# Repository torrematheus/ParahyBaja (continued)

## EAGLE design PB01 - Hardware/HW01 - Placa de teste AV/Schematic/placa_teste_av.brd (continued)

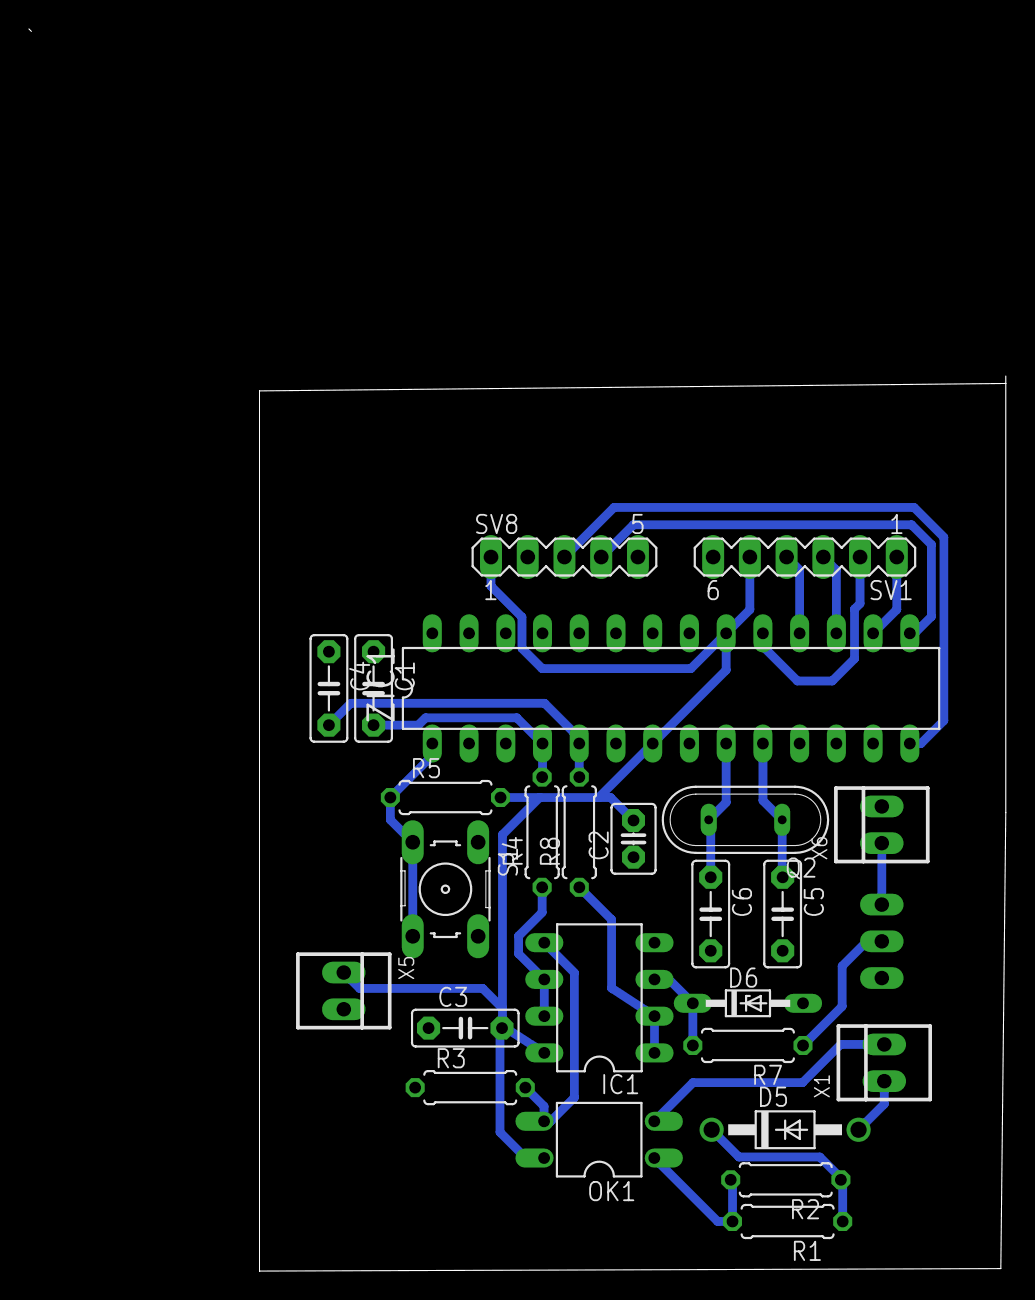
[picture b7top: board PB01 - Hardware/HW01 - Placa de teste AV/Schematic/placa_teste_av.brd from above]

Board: 2 copper layers, 51.6 x 61.4 mm, 26 parts (1 on the bottom side), 23 nets.

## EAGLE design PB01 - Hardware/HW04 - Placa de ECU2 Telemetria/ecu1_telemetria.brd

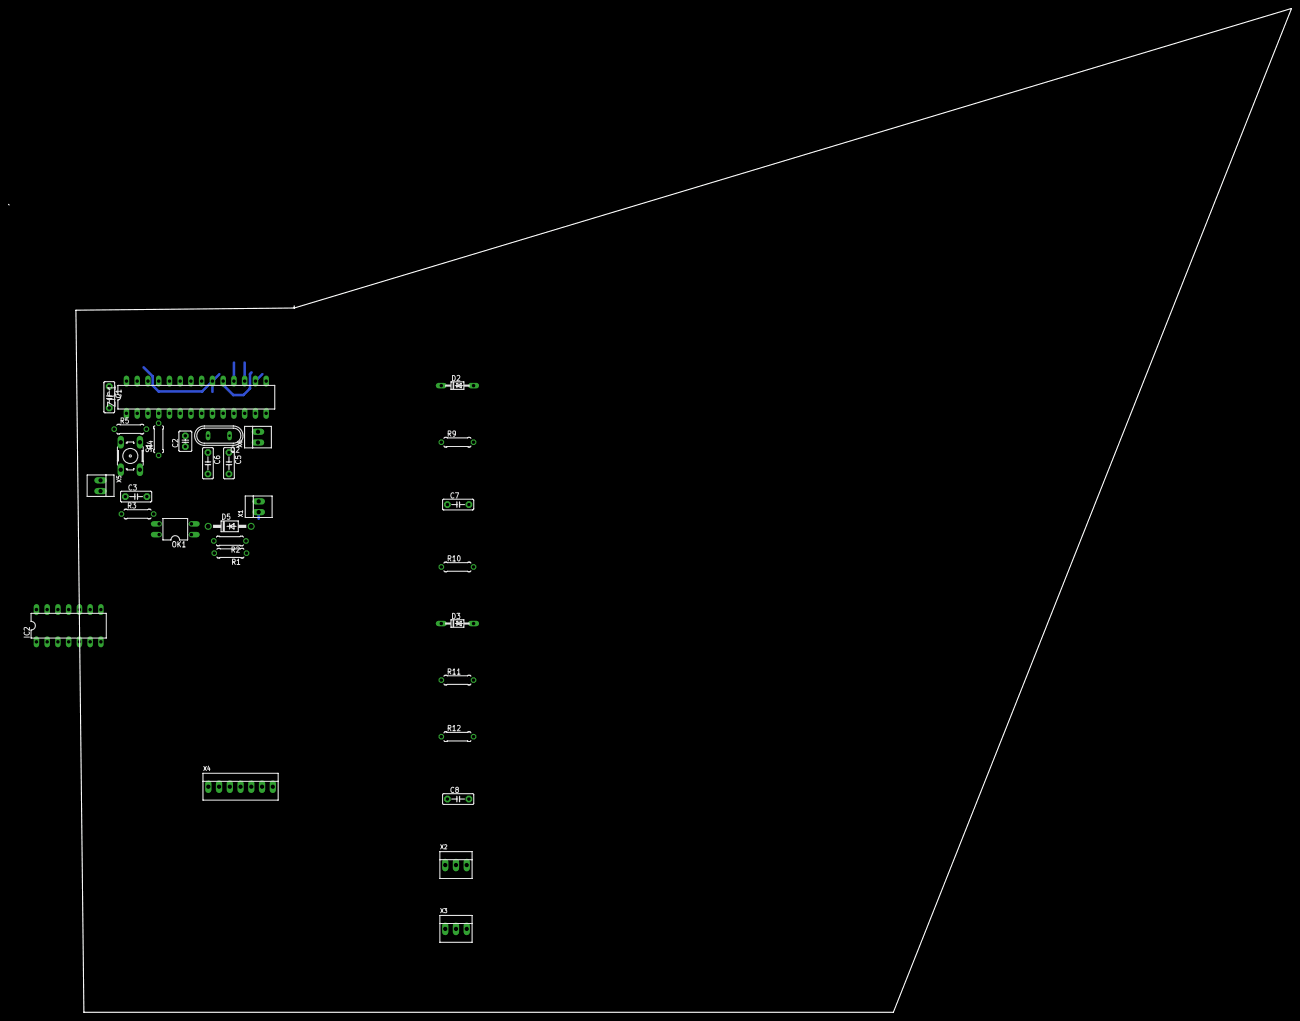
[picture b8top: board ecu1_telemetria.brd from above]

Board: 2 copper layers, 303.3 x 237.3 mm, 30 parts (0 on the bottom side), 25 nets.

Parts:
C1, C3, C7, C8: 100nF; C5B2.5
C2: 100nF; C2.5-3
C5, C6: 22pF; C5B2.5
D2, D3: 5.0V; DO34Z7
D5: 1N4004; DO41-10
IC2: LM324N; DIL14
OK1: PC817; DIL04
Q2: 16MHz; QS
R1, R2, R4, R10, R12: 1k; 0207/7
R3, R5: 10k; 0207/7
R9, R11: 4.7KR; 0207/7
S1: B3F-10XX
X1, X5, X6: 22-23-2021
X2, X3: 22-23-2031
X4: 22-23-2071
ZIC1: ATMEGA8; DIL28-3

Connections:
+5V: C2.2, C3.2, IC2.4, OK1.4, R5.2, X4.7, X5.1, ZIC1.7, ZIC1.20
+12V: X2.1, X3.1, X6.1
COMB1_IN: R9.1, X3.2
COMB1_OUT: C7.2, R10.2, ZIC1.5
COMB2_IN: R11.1, X2.2
COMB2_OUT: C8.2, R12.2
GND: C1.1, C2.1, C3.1, C5.2, C6.2, C7.1, C8.1, D2.A, D3.A, IC2.11, R3.1, S1.1, S1.2, X2.3, X3.3, X4.6, X5.2, X6.2, ZIC1.8, ZIC1.22
MISO: X4.4, ZIC1.18
MOSI: X4.3, ZIC1.17
unnamed: OK1.1, R1.2, R2.2
unnamed: D5.C, R1.1, R2.1
unnamed: IC2.1, IC2.2, R4.1
unnamed: D2.C, IC2.10, R9.2
unnamed: IC2.3, OK1.3, R3.2
unnamed: R5.1, S1.3, S1.4, ZIC1.1
unnamed: IC2.8, IC2.9, R10.1
unnamed: D3.C, IC2.12, R11.2
unnamed: IC2.13, IC2.14, R12.1
RPM_GND: OK1.2, X1.2
RPM_IN: D5.A, X1.1
RPM_OUT: C1.2, R4.2, ZIC1.4
SCK: X4.2, ZIC1.19
SS: X4.5, ZIC1.16
XTAL1: C6.1, Q2.2, ZIC1.9
XTAL2: C5.1, Q2.1, ZIC1.10

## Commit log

2019-08-21 Placa de teste AV
2019-08-21 Teste de AV
2019-08-21 Placa teste AV
2019-08-21 21/08/2019
    Adicionado o TCC de Matheus Torres, ajuste na simulação do teste AV
2019-08-23 Teste do Extensometro
2019-09-06 Placa ECU1 da telemetria
2019-09-06 ECU1
2019-09-11 Rename TestePlaca.ino to TestePlaca1.ino
2019-09-19 ECU 1 e 2 Telemetria
2019-09-19 TE#LEMETRIA
2019-09-20 TELEMETRIA
2019-10-07 Placa Leds RPM
2019-10-28 Placa de AV 2.0
2019-10-28 Placa AV 2.0
2019-10-28 teste de av 2.0
2019-11-07 BNE2019
2020-02-20 Códigos ECUs NAC20
2020-02-20 ECU1 NAC_2020
2020-02-21 ECU2_2020
